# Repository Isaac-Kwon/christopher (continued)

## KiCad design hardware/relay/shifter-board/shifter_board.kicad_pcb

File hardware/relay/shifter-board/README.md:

# 릴레이 시프터 보드 (Phase 3 R 트랙, 회로도)

작성일: 2026-11-15 · 상태: **회로도(KiCad 10) 생성·ERC·넷리스트 시뮬레이션 완료, 기판 배치(부품 배치 + 넷리스트 + 설계 규칙) 완료, 배선은 사용자가 나중에 함. 결정 0003 8.3절(S1–S3) 반영함(10절)** · 관련: `hardware/relay/concept.md` 3·5·7절, `docs/decisions/0001-test-register-timing.md`, `docs/decisions/0003-interfaces.md`(5.2·7.1·8.3절), `hardware/common/design-brief.md`, `hardware/common/unit-tester/README.md`, 기준 모델 `crates/christopher-core/src/relay.rs`

**표기.** **(계산)** = 이 문서의 산술, **(추정)** = 실측 전 값, **(미확인)** = 데이터시트로 확인하지 못한 것.

## 1. 무엇인가

`concept.md` 3.3절의 시프터 보드 **1장** = 이진 5단 시프터 **한 쌍**(가는 길 + 오는 길). 유닛당 4장(a1–a4). 한 단의 같은 선에서 가는 길 접점과 오는 길 접점은 **한 개의 DPDT 릴레이**가 함께 전환한다(두 반쪽이 코일을 공유). 보드 = 5단 × 26 = **릴레이 130개**, 코일 130개, 역기전력 다이오드 130개.

| 파일 | 내용 |
|---|---|
| `gen_shifter.py` | KiCad 프로젝트와 계층 회로도 생성기(표준 라이브러리만 사용). KiCad 표준 심볼 라이브러리에서 심볼을 복사해 넣는다 |
| `shifter_board.kicad_pro`, `shifter_board.kicad_sch` | 생성물. 루트 시트: 커넥터 5개 + 단 시트 5개 + `CHASSIS` 부품(장착 구멍 H1–H4, R6, C1) |
| `stage_1/2/4/8/16.kicad_sch` | 생성물. 단(이동량) 시트: 릴레이 26개 + 다이오드 26개 + 표시 LED |
| `verify_shifter.py` | 넷리스트를 읽어 보드를 시뮬레이션(5절) |
| `gen_shifter_pcb.py`, `shifter_board.kicad_pcb` | 기판 배치 생성기와 생성물(6절). 배선 없음 |
| `verify_shifter_pcb.py` | 배치된 기판 대 회로도 확인 + DRC(6절) |

생성물은 UUID를 고정해 두어 다시 생성해도 차이가 나지 않는다. 손으로 고치지 말고 생성기를 고친다.

## 2. 회로 규약 (`relay.rs`와의 대응)

- 선 번호 i = 0..25 ↔ 글자 A–Z. 네트 이름: `OIN_A`(가는 길 입력) … `OOUT_A`(가는 길 출력), `RIN_A`(오는 길 입력) … `ROUT_A`(오는 길 출력), 단 사이는 `O1_A`..`O4_A`, `R1_A`..`R4_A`.
- 단 b(b = 0..4, 이동량 s = 2^b, 시트 이름 `STAGE_s`, 참조 `K{b+1}{i+1:02}` = K101..K526), 선 i의 릴레이 하나:

| 접점 | 공통(COM) | 상시 닫힘(NC, 코일 off) | 동작 시 닫힘(NO, 코일 on) |
|---|---|---|---|
| 극 1 = 가는 길 반쪽 | 핀 4 ← 입력 `OIN_i` | 핀 3 → 출력 `OOUT_i` | 핀 5 → 출력 `OOUT_(i+s mod 26)` |
| 극 2 = 오는 길 반쪽 | 핀 9 ← 입력 `RIN_i` | 핀 10 → 출력 `ROUT_i` | 핀 8 → 출력 `ROUT_(i−s mod 26)` |

  (G6S-2 핀 기능은 KiCad 심볼 그림에서 확인: 코일 정지 상태에서 극 1의 접극자는 핀 3, 극 2는 핀 10에 닿아 있다. 코일 = 핀 1(+)과 12(−).)
- 한 단의 입력 → 출력, 단 0 → 단 4 순서로 직렬(덧셈은 교환 법칙이 성립하므로 순서 무관). 코일을 켠 단의 이동량 합이 제어값 a(0..25, 합이 25를 넘지 않음).
- **가는 길**: `OIN_i` → `OOUT_(i+a mod 26)`. `relay.rs`의 `shift_binary(c, a, reverse=false)`와 같다.
- **오는 길**: `RIN_i` → `ROUT_(i−a mod 26)`. 오는 길은 같은 제어값으로 가는 길의 시프트를 **되돌린다**(`relay.rs`의 `scramble`에서 가는 길의 `shift_binary(x, a, false)`마다 오는 길에 `shift_binary(x, a, true)`가 대응). 같은 코일이 두 극을 움직이므로 "제어를 따로 두지 않는다"는 concept 2.2절 ②가 그대로 성립한다.
- **모듈을 거꾸로 끼움**(`a4 = l`: 가는 길 −l, 오는 길 +l): 신호가 OUT 커넥터로 들어가 IN 커넥터로 나오면 가는 길 `OOUT_j` → `OIN_(j−a)`, 오는 길 `ROUT_j` → `RIN_(j+a)`. `verify_shifter.py`가 네 방향 모두 확인한다.
- 코일 구동: 단마다 `CTRLb`(24 V) 하나. 단의 코일 26개가 `CTRL`과 0 V 사이에 **병렬**, 코일마다 역기전력 다이오드(1N4148W, 음극 = `CTRL`). 단마다 표시 LED 하나(4.7 kΩ 직렬, 약 4.7 mA, `concept.md` 8절의 "단마다 LED 하나").
- 스크램블러는 유닛의 릴레이 구동기가 `CTRLb`에 24 V를 인가/차단한다(보드에는 능동 소자가 없다). 전환은 무전류 상태에서(`design-brief.md` 4.2절).

## 3. 커넥터와 핀 배치

보드 위 커넥터는 전부 **D-sub 수(핀) 직각 PCB 장착**(`Connector_Dsub:DSUB-37_Pins_Horizontal…`). 근거: `design-brief.md` 12절 결정 11(3.0은 D-sub 37), 시험기 J_A/J_B(암) 와 1:1 케이블로 바로 연결, 선 26개 + 기준선 3개가 37핀에 들어감. 4개를 한 모서리에 놓으면 폭이 맞지 않으므로(D-sub 37 ≈ 66 mm × 4) **IN 두 개(J1, J2)는 한 변, OUT 두 개(J3, J4)는 반대 변**에 놓는 것을 가정한다(변당 약 132 mm, `concept.md`의 160 × 200 mm 안에 듦 **(추정)**).

| 참조 | 이름 | 용도 | 핀 |
|---|---|---|---|
| J1 | OUTBOUND_IN | 가는 길 입력 | 1–26 = 선 A–Z, **27–29 = 0 V 기준선이지만 이 보드에서는 잇지 않음(미접속, `no_connect`)**, 30–37 예약(미접속) |
| J2 | RETURN_IN | 오는 길 입력 | 같음 |
| J3 | OUTBOUND_OUT | 가는 길 출력 | 같음 |
| J4 | RETURN_OUT | 오는 길 출력 | 같음 |
| J5 | CONTROL | 제어·구동(D-sub 9 수) | 1–5 = `CTRL0`..`CTRL4`(가중치 1, 2, 4, 8, 16, 24 V 단 구동), 6–7 = 0 V(**이 보드의 유일한 0 V 복귀**), 8–9 예약(미접속) |

핀 1–26 = 선 A–Z는 시험기 README 3.4절의 J_A/J_B와 같다(전원 핀 없음). 27–29번(0 V 기준선)은 **공통부 쪽(패널·레지스터·시험기)에서만 0 V에 묶고 스크램블러 쪽인 이 보드에서는 잇지 않는다**(결정 0003 5.2절: 양쪽에서 묶으면 코일 복귀 전류가 메뉴 케이블로 나뉘고 케이블을 뽑을 때마다 복귀 경로가 바뀐다). 제어값 a를 이진수로 `CTRL0`..`CTRL4`에 싣는다(비트 b = 이동량 2^b). 시험기는 J_C로 이 제어를 직접 구동하지 않는다. R.1에서는 유닛 쪽 구동기(또는 5개의 스위치 + 24 V)로 구동한다.

## 4. 코일 전류와 전력

릴레이: Omron G6S-2 급 24 V 코일(심볼 `Relay:G6S-2`, 풋프린트 `Relay_THT:Relay_DPDT_Omron_G6S-2`). `concept.md` 4절의 코일 전력 140–200 mW 사용 **(계산)**.

| 항목 | 140 mW | 200 mW |
|---|---:|---:|
| 코일 1개 (24 V) | 5.8 mA | 8.3 mA |
| 한 단 (26개 병렬 + LED 4.7 mA) | 약 157 mA, 3.7 W | 약 222 mA, 5.3 W |
| 최악(제어값 15 또는 23 = 4단 동작) | 약 0.63 A, 15 W | 약 0.89 A, 21 W |
| 평균(0–25 균등, 단 동작률 44%, `concept.md` 7절) | 8.0 W | 11.4 W |
| 유닛(보드 4장) 평균 | 32 W | 46 W |

`concept.md` 7절의 유닛당 32–46 W와 같은 값이다. 코일 한 단의 전류는 J5의 해당 핀 하나를 지난다(D-sub 접점 정격 수 A 이내). 0 V 복귀는 J5 핀 6–7뿐이다(신호 커넥터의 27–29는 잇지 않는다, 0003 S1). 접점 부하는 최대 약 0.2 A·24 V(`concept.md` 7절)로 G6S-2의 2 A·30 V DC 대비 여유가 크다.

## 5. 재생성과 검증

KiCad 10과 Python 3(표준 라이브러리만)이 필요하다. 표준 심볼 라이브러리 위치는 기본 `C:/Program Files/KiCad/10.0/share/kicad`, 다르면 환경 변수 `KICAD_SHARE`. `kicad-cli`는 PATH 또는 `KICAD_CLI`.

```
python gen_shifter.py                      # 회로도 재생성
kicad-cli sch erc --severity-all --format json -o erc.json shifter_board.kicad_sch
python verify_shifter.py                   # 넷리스트 내보내기 + 시뮬레이션 + 음성 시험
kicad-cli sch export pdf -o shifter_board.pdf shifter_board.kicad_sch   # 보고서용 PDF(저장소 밖에 둘 것)
```

- **ERC**(KiCad 10.0.4, 모든 심각도): 위반 **0건**(오류 0, 경고 0). 미사용 핀은 모두 비접속 표시(`no_connect`): J1–J4의 27–37, J5의 8–9.
- **시뮬레이션** `verify_shifter.py`: `kicad-cli`로 계층 넷리스트(kicadsexpr)를 내보내고, 제어값 0..25마다 J5 제어 네트에 코일 핀이 걸린 릴레이를 동작시켜 접점(NC/NO)을 닫은 뒤 합집합-찾기로 연결을 추적한다. 26개 선 × (가는 길, 오는 길, 거꾸로 끼운 가는 길·오는 길)이 `shift_binary`(코드에 옮겨 둔 `relay.rs` 사본)의 (i+a), (i−a), (j−a), (j+a) mod 26과 **정확히 같고 다른 연결은 없음**(우회·단락 없음)을 확인한다. 코일·다이오드 위상(단별 26개, 0 V, 다이오드 방향)과 부품 수(릴레이 130, 다이오드 130)도 확인한다. 0003 항목: J1–J4의 27–29번이 어느 넷에도 묶이지 않음, `CHASSIS`(H1–H4, R6.1, C1.1)가 0 V 넷과 별개이고 R6(1 MΩ) ∥ C1(10 nF)로만 0 V에 닿음, 어떤 제어값에서도 `CHASSIS`가 신호·제어 핀과 이어지지 않음. 결과: 26개 제어값 전부 통과.
- **음성 시험**: 넷리스트 복사본에서 J3 핀 3↔4, J1 핀 1↔2, J4 핀 20↔25, 릴레이 K305의 NC↔NO, J5의 CTRL1↔CTRL2를 바꾸면 모두 검증이 실패한다. 0003 항목으로 J1 핀 27·J4 핀 29를 0 V에 묶기, J5 0 V 핀을 `CHASSIS`에 단락, 장착 구멍 H3을 0 V로 옮기기, R6을 `CHASSIS` 쪽으로 옮기기도 모두 감지된다(10개 모두 감지).
- 회로도 PDF는 저장소 밖의 빌드 디렉터리(Windows: `%LOCALAPPDATA%\christopher\shifter-board`)에 둔다. 용지 A1, 루트 + 단 시트 5장 = 6쪽. `gen_shifter.py`는 `.kicad_pro`를 덮어쓰므로 곧바로 `gen_shifter_pcb.py`를 다시 돌린다.

## 6. 기판 배치 (배선은 사용자가 나중에 함)

범위: **배치만**. 외곽선, 장착 구멍, 모든 풋프린트의 위치·방향, 회로도 넷리스트(래츠넷이 보임), 설계 규칙. 동박 배선·비아·존은 없다(배선 코드는 생성기에 넣지 않았다, 플래그도 없다). `gen_shifter_pcb.py`는 `kicad-cli`로 회로도 넷리스트를 내보내 풋프린트를 KiCad 라이브러리에서 복사해 `shifter_board.kicad_pcb`를 쓰고(표준 라이브러리만 사용, UUID 고정이라 재생성 결과가 바이트 단위로 같다), 같은 이름의 `.kicad_pro`에 보드 설계 규칙을 병합한다. 주의: `gen_shifter.py`를 다시 돌리면 `.kicad_pro`가 덮어쓰이므로 그 뒤에 `gen_shifter_pcb.py`를 다시 돌린다.

**크기: 250 x 228 mm, 4층.** 160 x 200 mm는 들어가지 않는다. G6S-2 풋프린트의 courtyard가 7.9 x 15.3 mm여서 한 열 26개만 해도 26 x 8.0 = 208 mm이고(릴레이 130개의 면적만 약 1.6만 mm2), 선 26개 x 반쪽 2개의 단 사이 이동 배선(이동량 16 단은 위로/아래로 최대 약 21개의 수직 차선이 겹침 **(계산)**)과 커넥터 부채꼴 배선 공간이 더 든다. 그래서 단 사이를 38 mm 간격으로 비워 두었다(배선 채널). 유닛 카드 케이지(`concept.md`)는 이 크기로 바꿔야 한다. 채널 폭은 배선하면서 줄일 수 있다(릴레이 열 사이 간격 38 mm, 행 간격 8.0 mm는 `gen_shifter_pcb.py` 상단 상수).

배치 규칙:
- 릴레이 5열(단 1, 2, 4, 8, 16, 왼쪽에서 오른쪽) x 26행(선 A가 위). 90도 돌려서 신호 흐름이 +x 방향: 핀 순서 1(코일), 3(NC), 4(COM), 5(NO)가 가는 길 행(y), 핀 12, 10, 9, 8이 5.08 mm 위의 오는 길 행. 행 간격 8.0 mm(courtyard 7.9 mm), 열 간격 38 mm.
- 코일 역기전력 다이오드(SOD-123): 각 릴레이의 코일 핀 왼쪽에 세로로(음극이 핀 1 쪽). 왼쪽 6 mm 띠에 단별 CTRL/0 V 수직 레일을 둘 자리가 있다.
- 단 표시용 R + LED: 각 열 아래.
- 커넥터: 왼쪽 변에 J1(가는 길 IN), J2(오는 길 IN), J5(제어, D-sub 9), 오른쪽 변에 J3, J4(OUT). IN은 한 변, OUT은 반대 변. 장착 구멍 M3 4개(모서리, **도금 구멍 `MountingHole_3.2mm_M3_Pad` = 회로도 부품 H1–H4, 넷 `CHASSIS`**), 단 이름 실크. `CHASSIS`–0 V의 R6·C1은 오른쪽 아래.
- `CHASSIS` 넷: D-sub 5개의 껍데기 패드(`SH`, 커넥터마다 2개, 회로도 심볼에는 핀이 없음)와 H1–H4. 생성기가 `SH` 패드에 `CHASSIS`를 붙이고 `verify_shifter_pcb.py`가 같은 규칙으로 회로도 대 기판을 비교한다.
- 같은 규칙으로 정한 층 계획(배선 때 쓰라고 남기는 제안, 강제 아님): 가는 길은 F.Cu(수평)·In1(수직), 오는 길은 B.Cu(수평)·In2(수직), 코일 CTRL 레일 In1, 0 V 레일 In2. 이동 배선은 차선+비아 방식(이동량 s 단의 수직 차선은 가는 길/오는 길 각각 약 3, 5, 9, 17, 21개). 커넥터 팬아웃은 핀 열(1-19, 20-26)별로 단조이므로 층을 나눠 비아 없이 가능하다.

설계 규칙(`.kicad_pro`, 저가 4층 업체 표준): 선폭/간격 0.15 mm, 비아 0.5/0.25 mm(환형 0.125), 구멍 간 0.25 mm, 동박-외곽 0.3 mm. 넷클래스 Default(선폭 0.2)와 Coil(`/CTRL*`, `/GND`, 선폭 0.6 mm: 단 코일 전류 최대 약 0.25 A, 보드 전체 0 V 복귀 최대 약 0.9 A 이므로 0 V 간선은 더 두껍게). 신호 전류는 선 하나 약 10 mA라 0.15-0.2 mm로 충분하다.

확인(`verify_shifter_pcb.py`, 결과 PASS):
- 회로도 부품 281개(275 + H1–H4 + R6 + C1) 전부 기판에 있고 풋프린트가 회로도와 같으며(여분 없음), IPC-D-356 넷리스트의 패드 연결이 회로도 넷과 정확히 같음(1490 패드, `CHASSIS`의 `SH` 패드 10개 포함). 패드 두 개의 넷을 바꾼 복사본, D-sub 껍데기 패드 하나를 `CHASSIS`에서 0 V로 옮긴 복사본은 검출됨(음성 시험 2건). 재생성 결과는 바이트 단위로 같음.
- `kicad-cli pcb drc`(모든 심각도): **위반 0건**(courtyard/겹침/외곽/간격 포함), 연결 안 됨 항목만 존재. 보고서의 연결 안 됨 목록은 약 500건에서 잘리므로(499건 표시) 래츠넷 수는 pcbnew 연결성으로 센다: **1125** = Σ(핀 수 − 1) (회로도 넷 기준 1115 + 껍데기 패드 10).
- 렌더(`kicad-cli pcb render`)와 PDF를 빌드 디렉터리에 둠. 가버/드릴은 배선 후에(저장소 밖 `%LOCALAPPDATA%\christopher\shifter-board`).

```
python gen_shifter_pcb.py
python verify_shifter_pcb.py
kicad-cli pcb render --side top --width 2400 --height 2200 -o <빌드 디렉터리>/render_top.png shifter_board.kicad_pcb
```

### 6.1 S4 변형 (`--variant s4`, 앞을 보는 a4용)

`python gen_shifter_pcb.py --variant s4` → **`shifter_board_s4.kicad_pcb`**(+ `.kicad_pro`). 회로도·넷리스트는 `shifter_board.kicad_sch` 그대로(패드 넷이 표준 기판과 완전히 같음), 외곽 250 x 228, 구멍 4개, 릴레이·다이오드·표시등·R6·C1·J5도 표준과 같은 자리다. 바뀌는 것은 **J1–J4뿐**이다:

| 커넥터 | 표준 (앞면 F.Cu) | S4 변형 (**뒷면 B.Cu**, 거울) |
|---|---|---|
| J1 | 왼쪽 변, 핀 1 위(y 22.28), 회전 270 | 왼쪽 변, 핀 1 아래(y 72.13), 회전 90 |
| J2 | 왼쪽 변, y 96.29, 회전 270 | 왼쪽 변, y 146.14, 회전 90 |
| J3 | 오른쪽 변, y 72.13, 회전 90 | 오른쪽 변, y 22.28, 회전 270 |
| J4 | 오른쪽 변, y 146.14, 회전 90 | 오른쪽 변, y 96.29, 회전 270 |

핀 행(49.86 mm)의 중심과 변, 몸체가 보드 밖을 향하는 방향은 같고(핀 위치를 pcbnew로 읽어 확인: 변형의 J1 핀 1·19·20이 표준 J3의 같은 핀 좌표와 같음) **핀 1의 끝만 반대**다. 신호 배정(J1 가는 길 IN, J2 오는 길 IN, J3 가는 길 OUT, J4 오는 길 OUT)은 그대로다.

왜 뒷면 거울인가: 앞을 보는 카드는 뒤를 보는 카드와 반대쪽에서 보이므로, 표준 기판을 앞으로 꽂으면 S4.J1–U.J3, S4.J2–W_L.J4, S4.J3–W_L.J1, S4.J4–U.J2의 양 끝 소켓에서 핀 1이 반대 끝에 온다(D-sub는 키가 있어 리본을 뒤집을 수 없다). 평면 회전(180도 또는 좌우 바꿈)은 쌓기에서의 변·자리를 바꾸거나 같은 결과를 내므로, 핀 1의 끝을 돌리는 것은 부품면을 바꾼 거울뿐이다. 부수 효과: S4의 소켓이 뒤를 향해 S4 점퍼가 25 / 50 mm가 된다(표준이면 앞면 쪽 +14로 39 / 64). 실크에 큰 글씨로 `S4 / a4 - FRONT`와 거울 표시가 있다. `verify_shifter_pcb.py`는 두 기판 모두 DRC 0건, 패드 넷 = 회로도, 래츠넷 1125, 재생성 바이트 동일을 확인하고, 변형이 표준과 J1–J4(뒷면, 핀 1 반대 끝, 핀 행 중심 유지) 외에 같음과 실크 표시를 확인한다. 쌓기에서 핀 1 정렬은 `wiring-cards/verify_cards.py`.

### 6.2 표준 기판에 커넥터만 뒷면으로 납땜하면? (검토 후 **기각**)

생각: S4도 표준 기판을 쓰고 J1–J4(직각 D-sub)를 뒤집어 뒷면에서 같은 구멍에 꽂는다(별도 기판 없음). 커넥터 몸체가 보드 밖을 향해야 하므로 몸체 축(핀 행에 수직)을 중심으로 돌려 꽂는 것만 가능하고, 핀 행 방향 좌표가 거울이 되며 두 핀 행은 그대로다. 풋프린트의 실제 패드 좌표(행 1 = 핀 1–19, y 0, 간격 2.77; 행 2 = 핀 20–37, y 2.84, 반 칸 어긋남)로 구한 **σ**(뒷면 커넥터의 핀 k가 들어가는 표준 구멍의 핀 번호):

| 행 | σ(k) |
|---|---|
| 1 (k = 1..19) | 20 − k (1↔19, 2↔18, …) |
| 2 (k = 20..37) | 57 − k (20↔37, 21↔36, …) |

표준 기판의 동박·넷은 구멍에 고정이므로 뒷면 커넥터의 핀 k는 표준 핀 σ(k)의 넷을 싣는다. 점퍼는 곧은 1:1 리본이라 이웃 카드(표준 커넥터)의 핀 k = 선 k가 S4의 핀 k에 닿는다. 결과: **선 A–S(핀 1–19)는 거꾸로(A↔S, B↔R, …) 연결되고 선 T–Z(핀 20–26)는 S4의 31–37번(비접속) 구멍으로 가서 끊긴다**(S4의 선 T–Z는 핀 31–37에 나와 이웃 카드의 31–37번은 연결이 없다). 커넥터의 역할(J1 = 가는 길 입력 …)은 구멍이 같으므로 바뀌지 않는다. 핀 1의 끝은 뒤집히므로 앞을 보는 카드라면 14가닥의 핀 1 정렬은 맞는다(S4 변형과 같은 끝). 그러나 전기적으로는 틀린다.

`wiring-cards/verify_cards.py`(`back_assembled_study`)가 풋프린트 패드 좌표에서 σ를 구해 같은 합성 유닛에 넣었다(리본 끝의 핀 k를 구멍 σ(k)에 연결):

| S4 방향 | 핀 1 정렬(점퍼 14가닥) | 합성 유닛 대 스크램블러 |
|---|---|---|
| 앞 | 14/14 정렬 | 60 Enigma I 순서 × 10 위치 = 600건 0건 일치(선의 약 9%만 맞음), 한 순서 전수 17,576 위치 0건 일치 |
| 뒤 | 4가닥(S4.J1–J4) 어긋남 | 같은 600건 0건 일치, 전수 0건 일치(a4가 거꾸로가 아닌 이중 오류) |

σ는 한쪽 끝만 바뀌는 순열이 아니라 **일부 선이 끊기는** 사상이어서 쌓기에서 흡수할 수 없다(이웃 카드 W·U도 같은 방식으로 뒤집으면 핀 1이 다시 어긋나고, 14가닥 전부가 W·S3 등 다른 카드와 이어져 있다). 흡수하려면 핀 k ↔ σ(k)로 엇갈린 맞춤 케이블 4가닥이 필요한데, 압접 리본은 1:1 곧은 선이라는 설계(3.4절)에 반한다. 따라서 **S4는 6.1절의 변형 기판**(핀 번호가 커넥터를 따라 돌아가므로 패드 n = 선 n)을 쓴다. 변형 기판은 커넥터가 뒷면에 있고 *패드 번호가 풋프린트의 거울을 따라가며 넷이 그 패드에 붙는다*는 점이 이 안과 다르다.

### 6.3 그 밖에 검토한 안 (2026-11-15, 사용자 결정: **변형 기판 유지**)

| 안 | 내용 | 판단 |
|---|---|---|
| 둥근 D-sub 케이블 | 표준 기판 그대로, S4 둘레 4곳만 암-암 1:1 둥근 케이블(자유롭게 꼬이므로 핀 1 문제 없음) | 전기적으로는 맞다. 그러나 지름 약 10 mm, 후드 약 15 mm, 굽힘 반경 수 cm라 25 mm 카드 간격 안에 못 들어가 적층 밖으로 고리를 내야 함(유닛당 4개, 12유닛 48개). 기각. R.1에서 변형 기판 주문 전 임시 시험용으로만 쓸 수 있음 |
| 한 기판에 D-sub 8개(듀얼 풋프린트) | 표준 J1–J4와 변형 J1–J4를 한 기판에 두고 한 세트만 실장 | 같은 자리: D-sub 구멍 배열이 대칭이라 두 세트의 구멍이 겹치는데 구멍마다 넷이 달라 불가. 변을 따라 다른 자리: 왼쪽 변에 남는 길이 약 36 mm(D-sub 37은 70.4 mm), 이웃 카드 커넥터와 마주 보지 않아 곧은 리본이 안 됨. 안쪽으로 약 5 mm 물린 뒷면 겹침(패드 Ø1.6, 열 간격 2.84 mm라 이만큼 필요)만 가능하지만 짝 면이 기판 끝보다 안쪽이 되어 IDC 플러그 간섭·이웃 카드와 5 mm 어긋남, 신호 104가닥이 패드 두 곳씩이라 배선 밀도 두 배. 얻는 것은 기판 종류 하나 감소뿐. 기각 |

## 7. 열린 질문

1. **코일 극성.** G6S-2(단안정, 극성 있음 **(미확인)**)의 코일 + 단자가 핀 1인지 데이터시트로 확인. 회로도는 핀 1 = +, 핀 12 = −로 가정(다이오드 방향 포함).
2. **부품 확정.** 24 V 코일 품번(`G6S-2` 24 VDC 계열), 풋프린트 `Relay_THT:Relay_DPDT_Omron_G6S-2`(관통 구멍)의 장착 면적 대 SMD 변형(`G6S-2F/-2G`), 호환품 사용 여부(`concept.md` 12절 위험 7).
3. **보드 크기와 커넥터 배치.** 160 × 200 mm에는 들어가지 않음(6절): 250 × 228 mm로 배치함, 유닛 카드 케이지 치수 갱신 필요. 배선 후 채널을 좁혀 줄일 수 있음. IDC 2 × 20 대안은 미검토.
4. **배선: 사용자가 나중에 함(6절의 층 계획 참고).** **배선 혼잡.** 단 16(±16칸)과 단 8의 교차 배선이 가장 길다. 선 순서대로 릴레이를 한 줄에 놓고 층수(4층?)·선 폭을 정한다. 직렬 접점 5개(반쪽당)의 접촉 저항 누적과 24 V 신호 간격.
5. **역기전력 다이오드와 복귀 시간.** 다이오드만 쓰면 복귀가 느리다(`decision 0001`의 3–5 ms **(추정)**). 시험 후 필요하면 다이오드 + 제너 또는 저항 병렬.
6. **보호.** (닫힘, 0003 S3) 이 보드에는 퓨즈·역극성 보호·TVS를 두지 않는다. 전원 입력이 없고 `CTRL` 선은 계수기 유닛 보드의 퓨즈(4 A) 뒤다(0003 6절, 7.3절). 접지는 `CHASSIS`(10절 참고).
7. **거꾸로 끼우기의 실현.** 커넥터가 IN/OUT 반대 변이라 보드를 뒤집어 끼우는 방식은 아니다. a4(가는 길 −l)는 케이블/백플레인에서 IN과 OUT을 맞바꿔 연결하는 것으로 구현한다(시뮬레이션은 이 방향도 검증함). 백플레인 설계에서 확정.
8. **시험점·표시.** 선별 시험점, 단 LED 위치, 참조 번호 실크(K101..K526 읽기 쉬운 배치), 단 LED 저항값(4.7 kΩ) 확정.
9. **시험기 연동.** (닫힘, 0003 S1) 27–29번은 공통부(시험기 포함) 쪽에서만 0 V에 묶고 이 보드에서는 잇지 않는다. 시험기의 J_A/J_B 27–29 = GND_F는 그대로다.

## 10. 결정 0003 반영 (8.3절)

| # | 변경 | 상태 |
|---|---|---|
| S1 | J1–J4의 27–29번을 0 V에서 뗌(`no_connect`). 0 V의 복귀는 J5의 6–7번만 | 적용. `verify_shifter.py`가 27–29번의 무연결을 검사하고 음성 시험 2건(J1.27, J4.29를 0 V에 묶기) |
| S2 | 껍데기(J1–J5)와 장착 구멍(H1–H4)을 `CHASSIS`로, `CHASSIS`–0 V에 R6 1 MΩ ∥ C1 10 nF/100 V | 적용. 루트 시트에 H1–H4(`Mechanical:MountingHole_Pad`, 도금 M3), R6, C1. 껍데기 패드 `SH`는 심볼에 핀이 없어 기판 생성기가 `CHASSIS`를 직접 붙이고 검증기가 같은 규칙으로 확인. 음성 시험 3건(0 V 핀을 `CHASSIS`에 단락, H3을 0 V로, R6을 `CHASSIS` 쪽으로) + 기판 음성 시험 1건(껍데기 패드를 0 V로) |
| S3 | 7절 6번(보호)·9번(27–29번)을 닫음. 보드에 퓨즈를 두지 않음 | 적용(7절의 6번·9번) |
| S4 | 바뀌지 않는 것: 암수(핀), J1–J4의 1–26번, J5의 핀 배치, 릴레이·다이오드 | 확인(시뮬레이션 26값 × 4방향 통과) |

장착 구멍은 도금 구멍이 되었다(풋프린트 `MountingHole_3.2mm_M3_Pad`). 금속 기둥으로 프레임(PE)에 닿게 하는 것은 기구 설계의 몫이다.

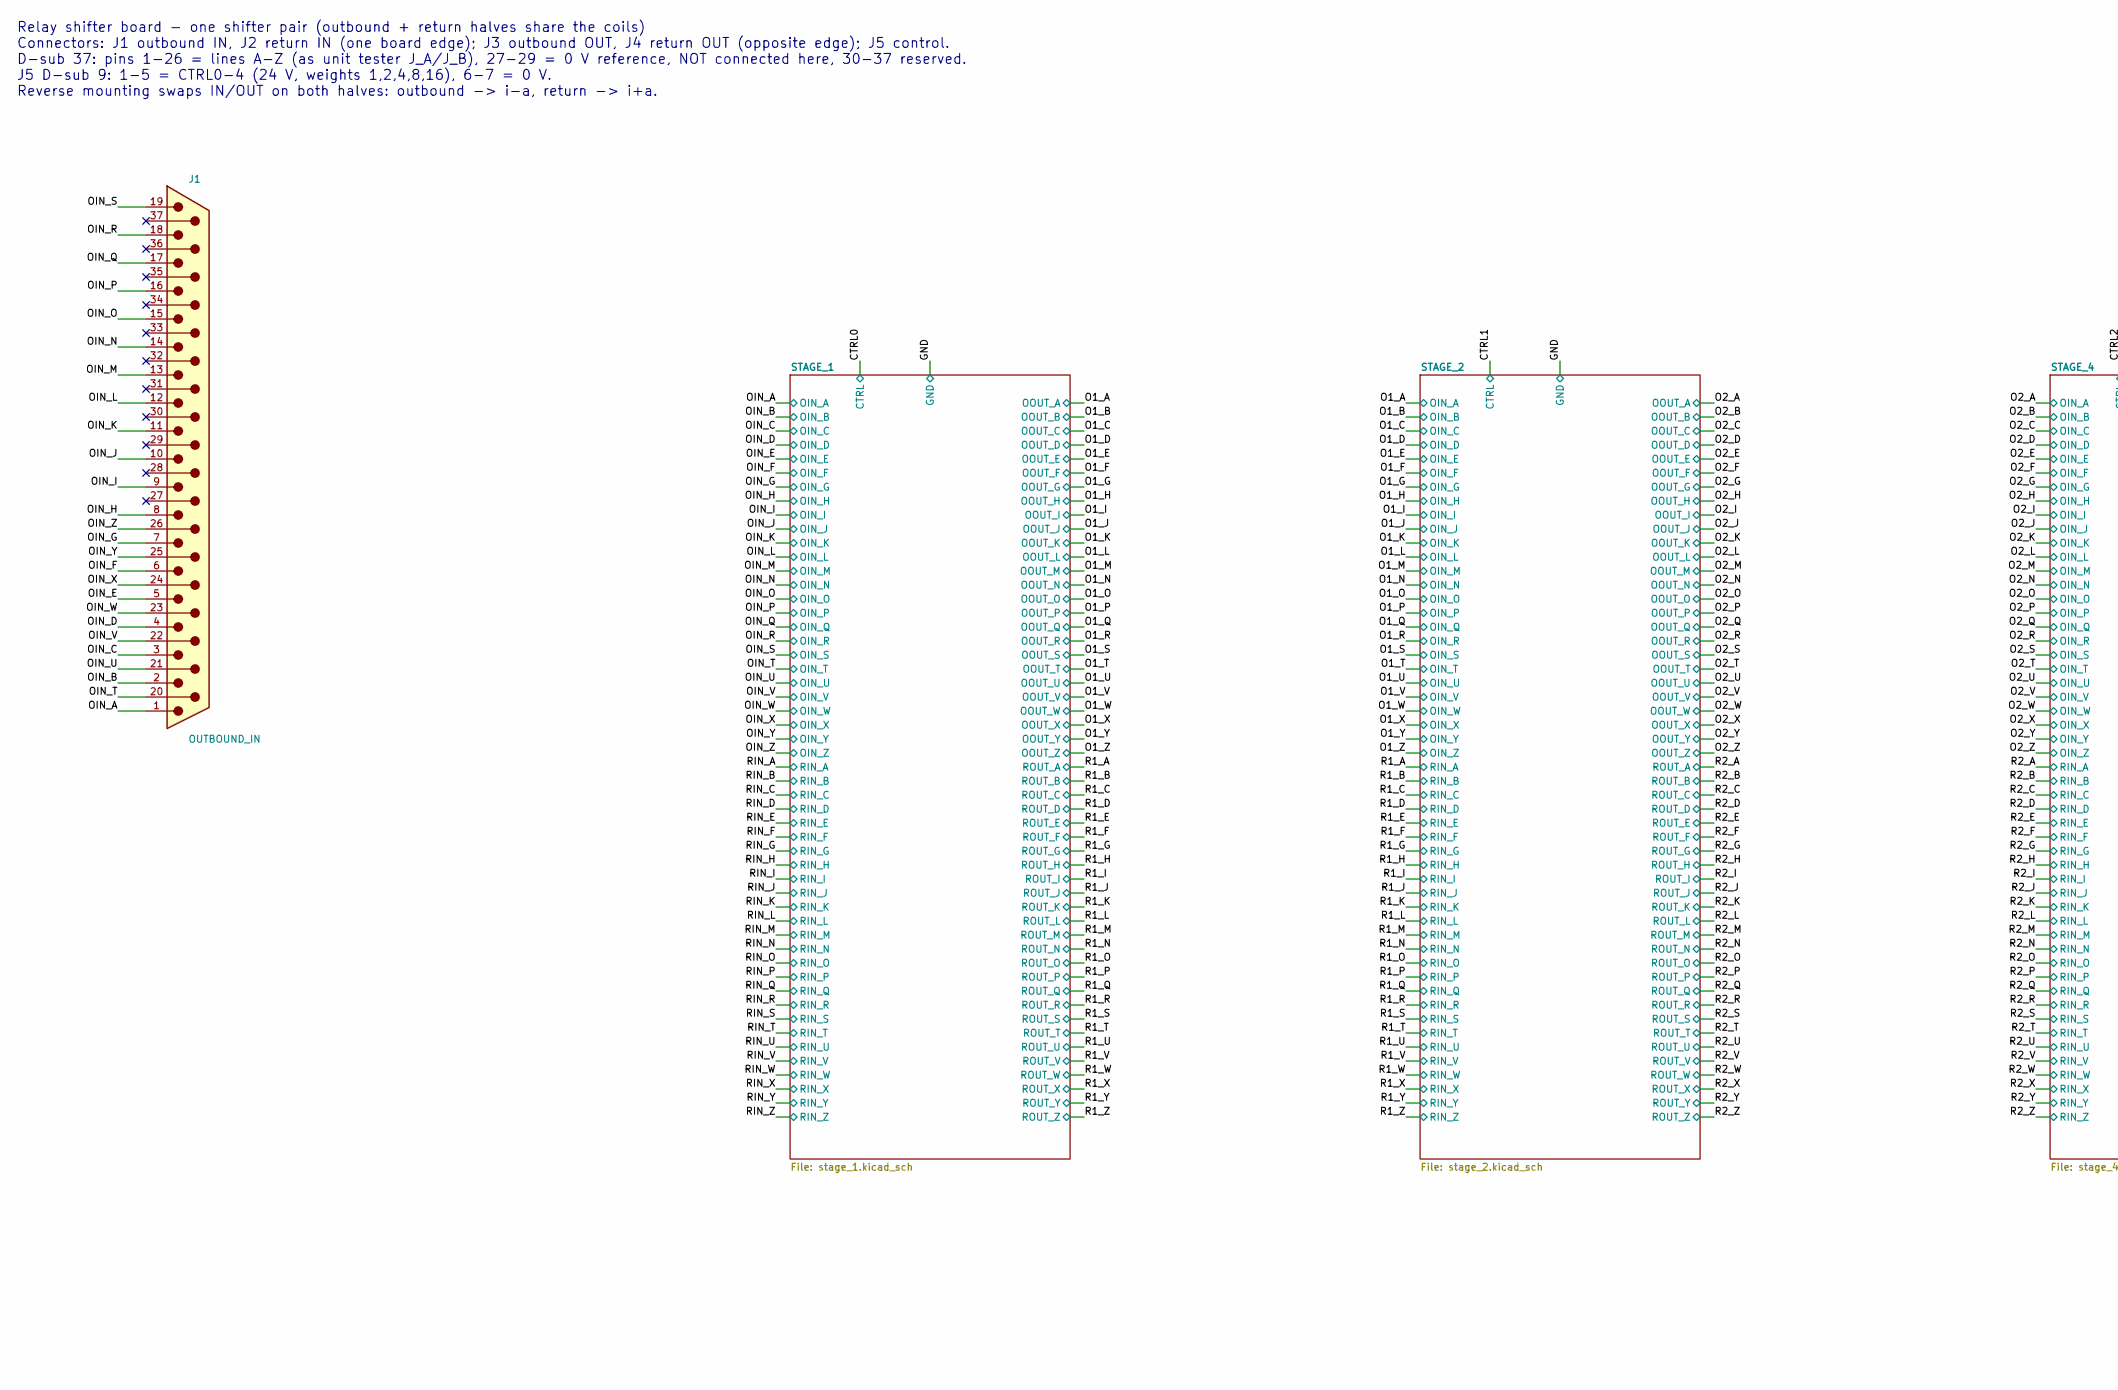
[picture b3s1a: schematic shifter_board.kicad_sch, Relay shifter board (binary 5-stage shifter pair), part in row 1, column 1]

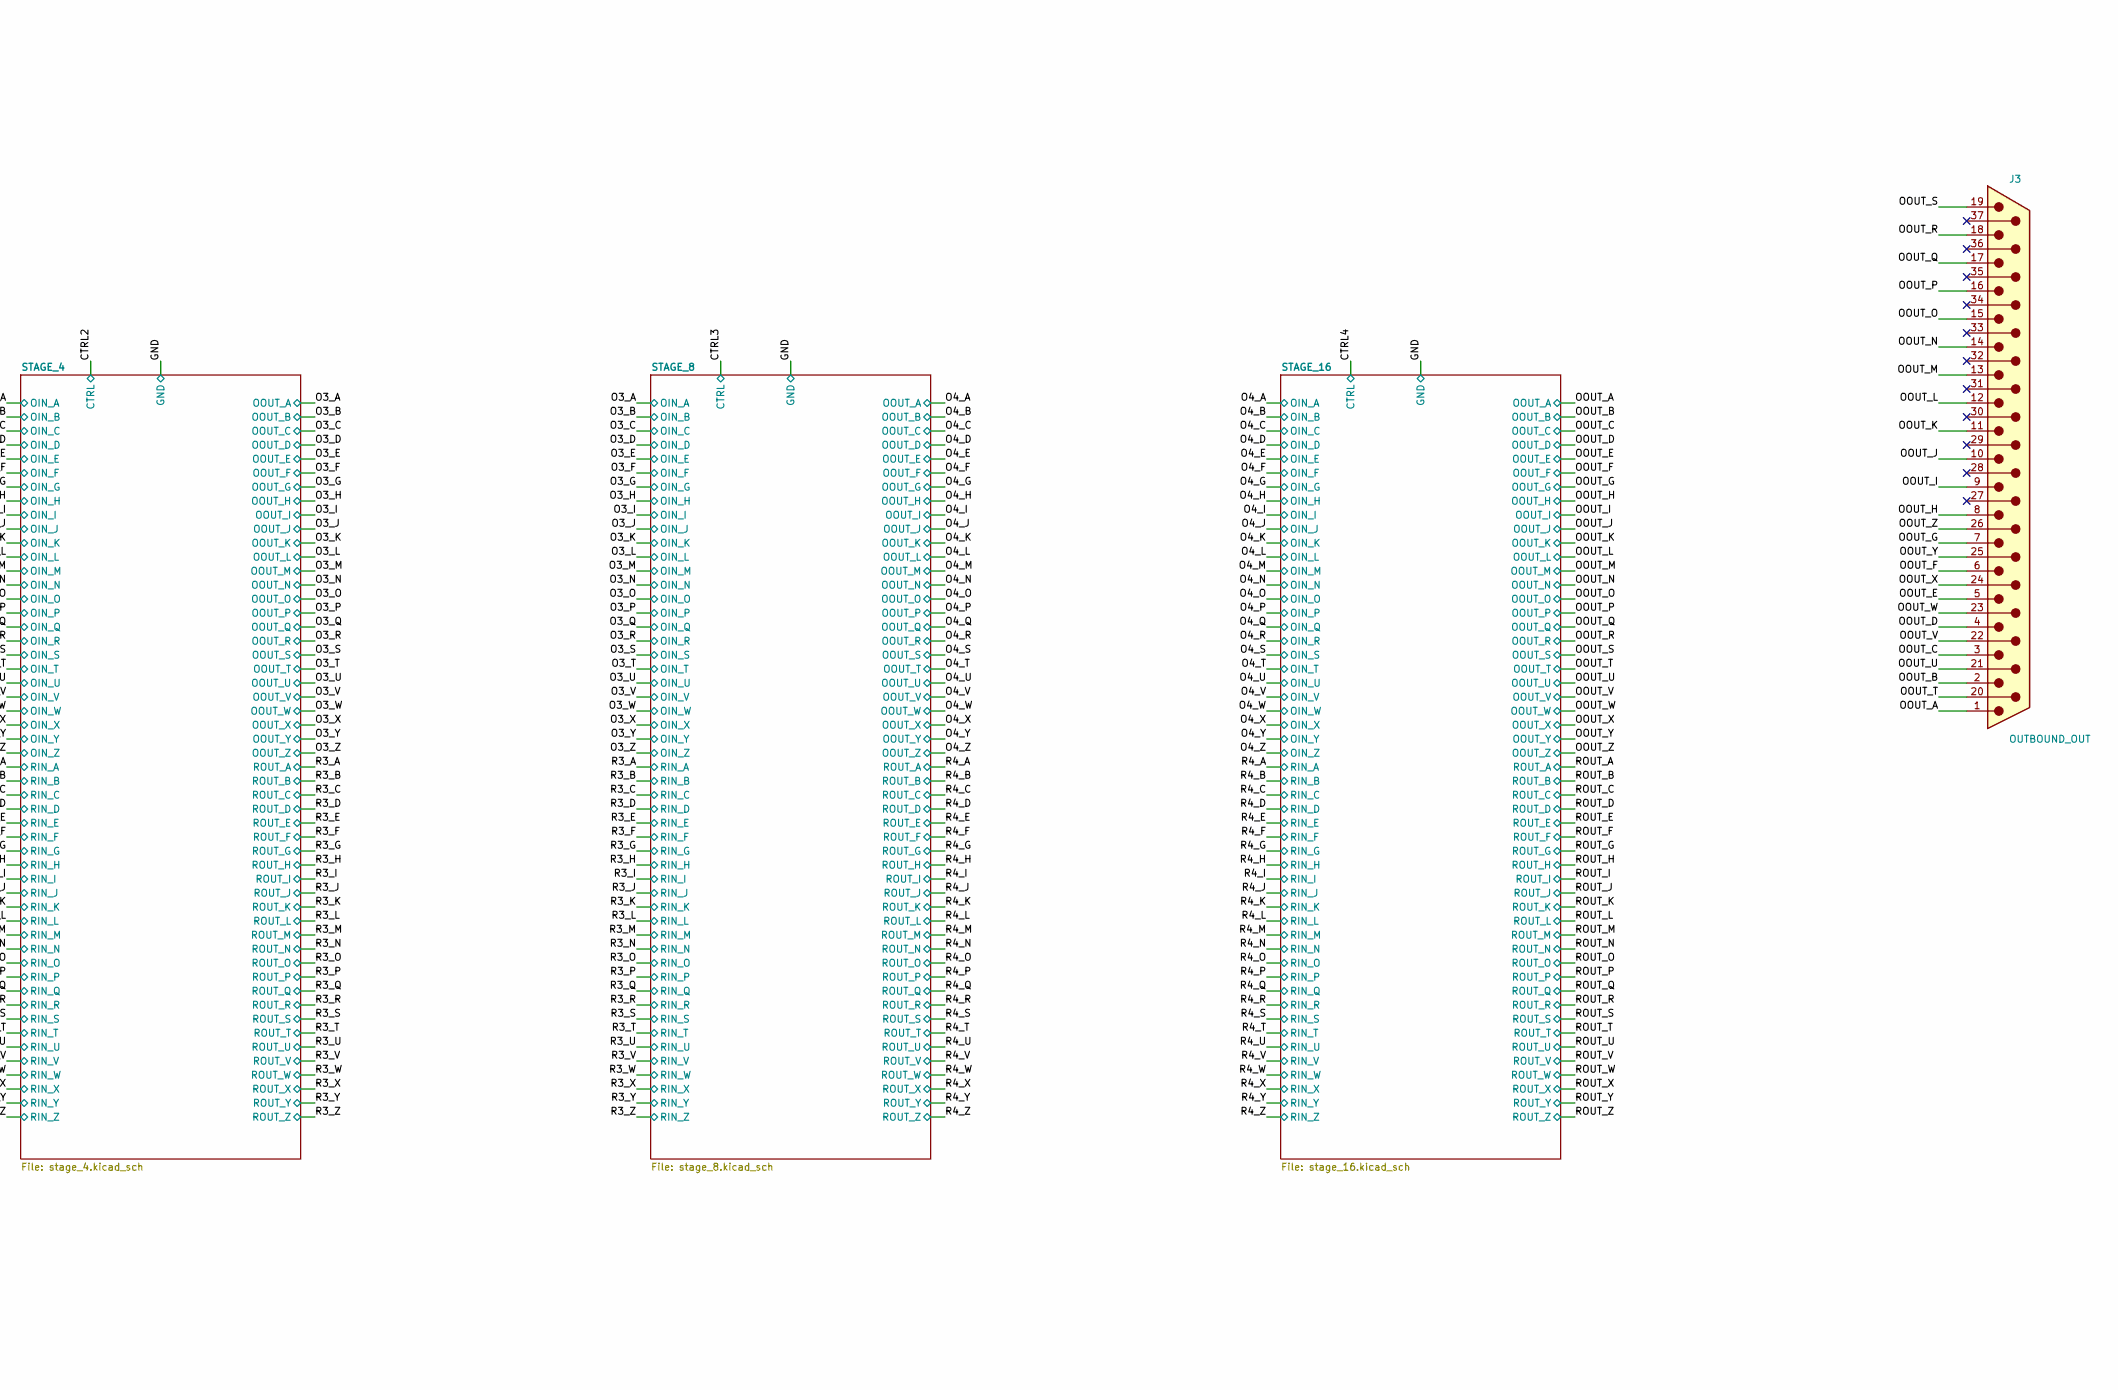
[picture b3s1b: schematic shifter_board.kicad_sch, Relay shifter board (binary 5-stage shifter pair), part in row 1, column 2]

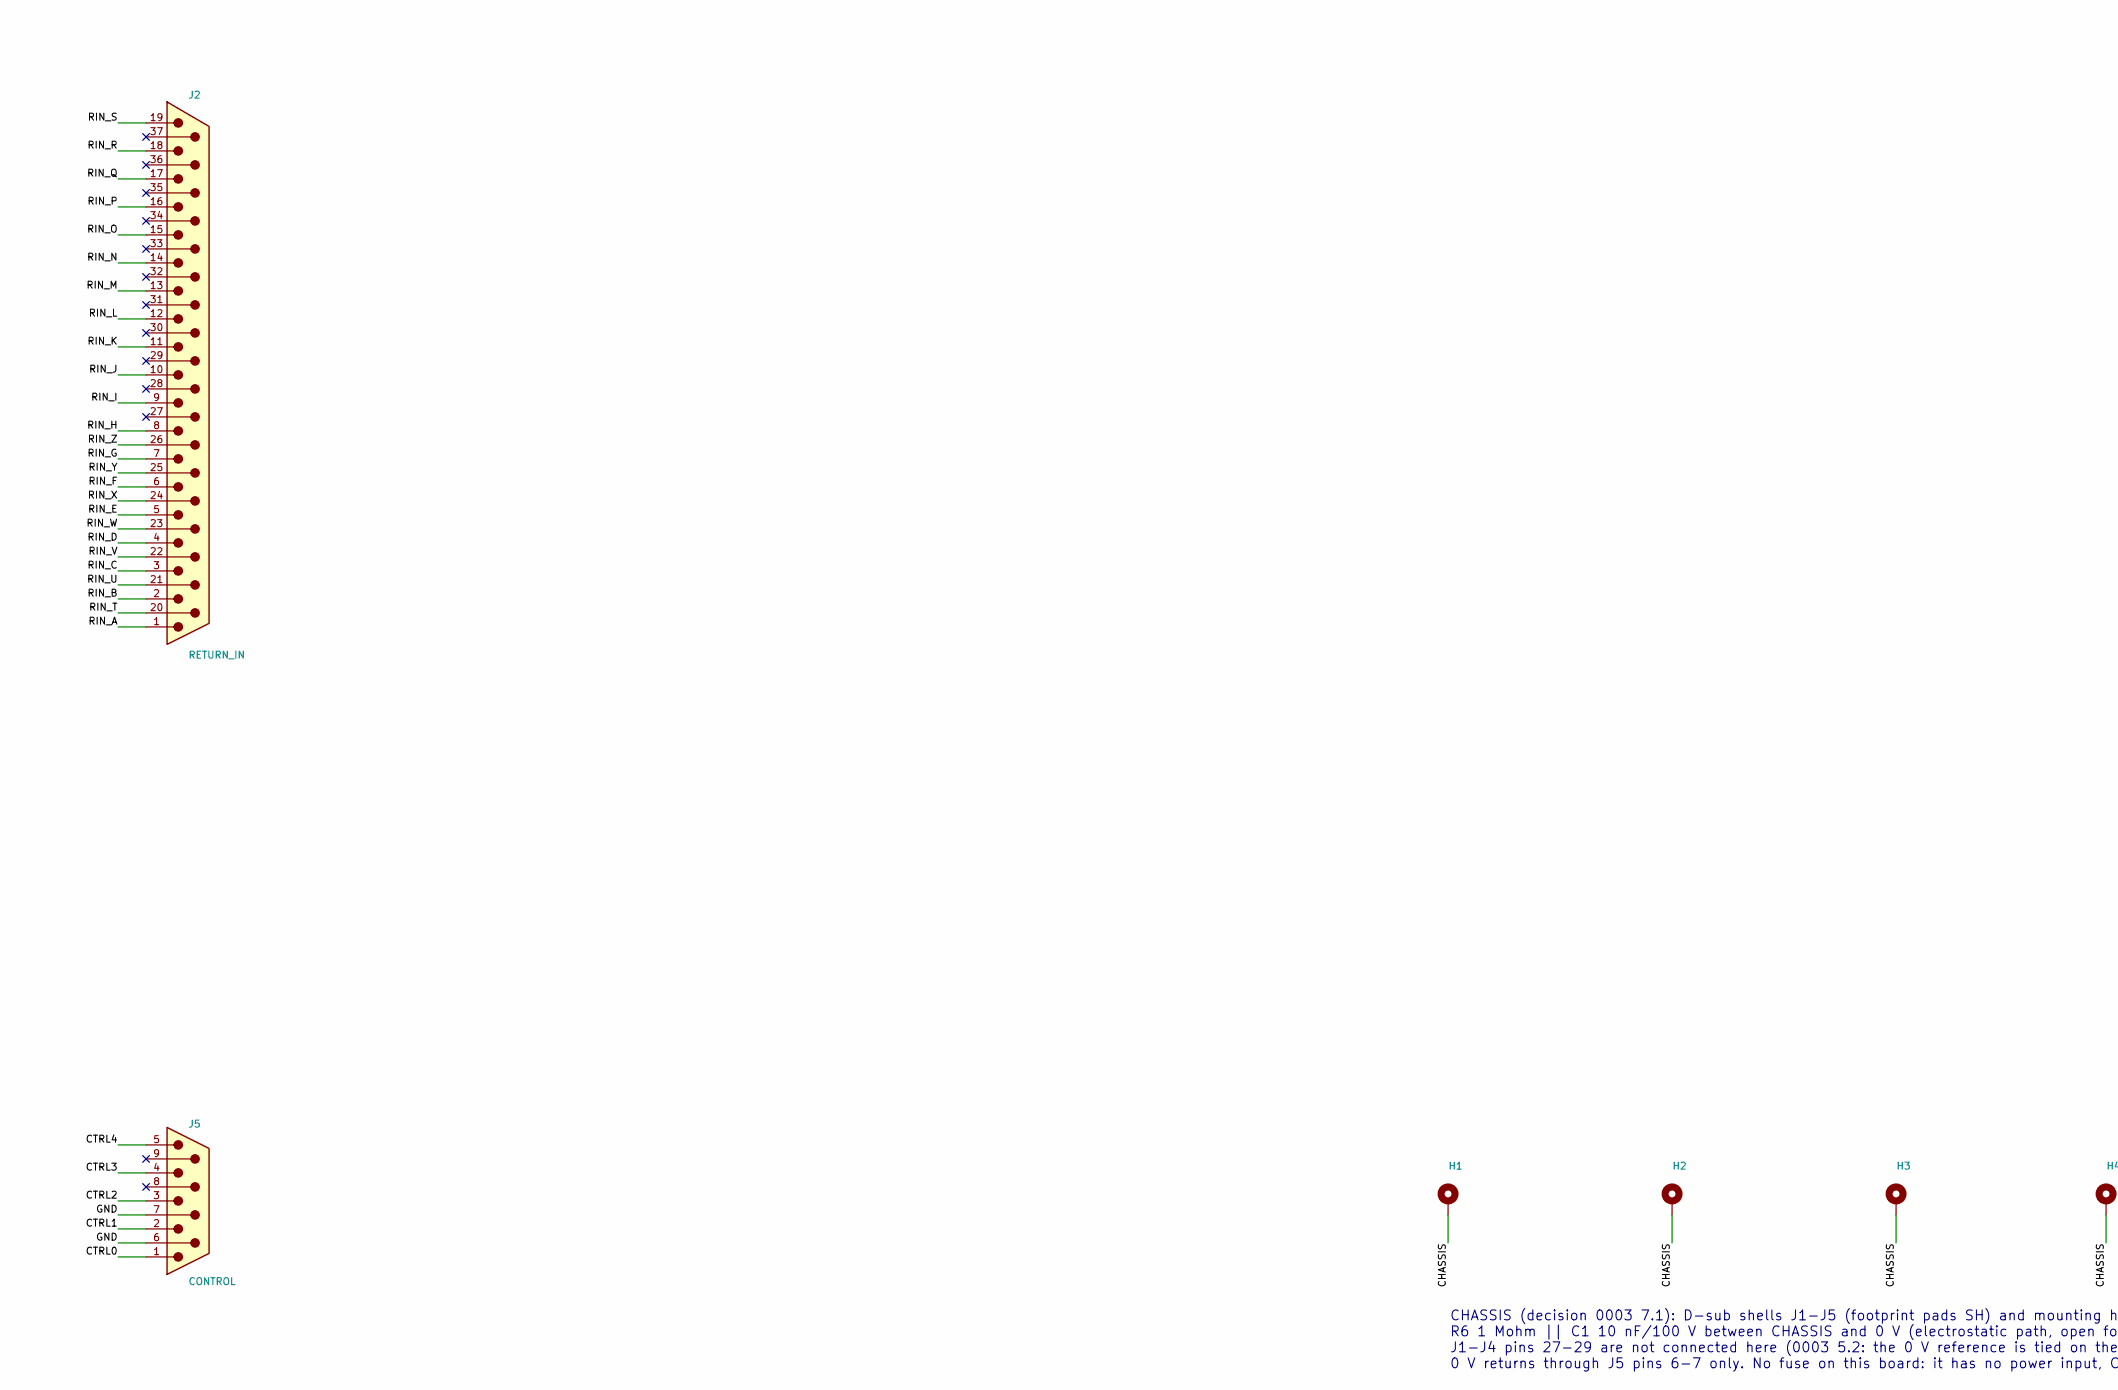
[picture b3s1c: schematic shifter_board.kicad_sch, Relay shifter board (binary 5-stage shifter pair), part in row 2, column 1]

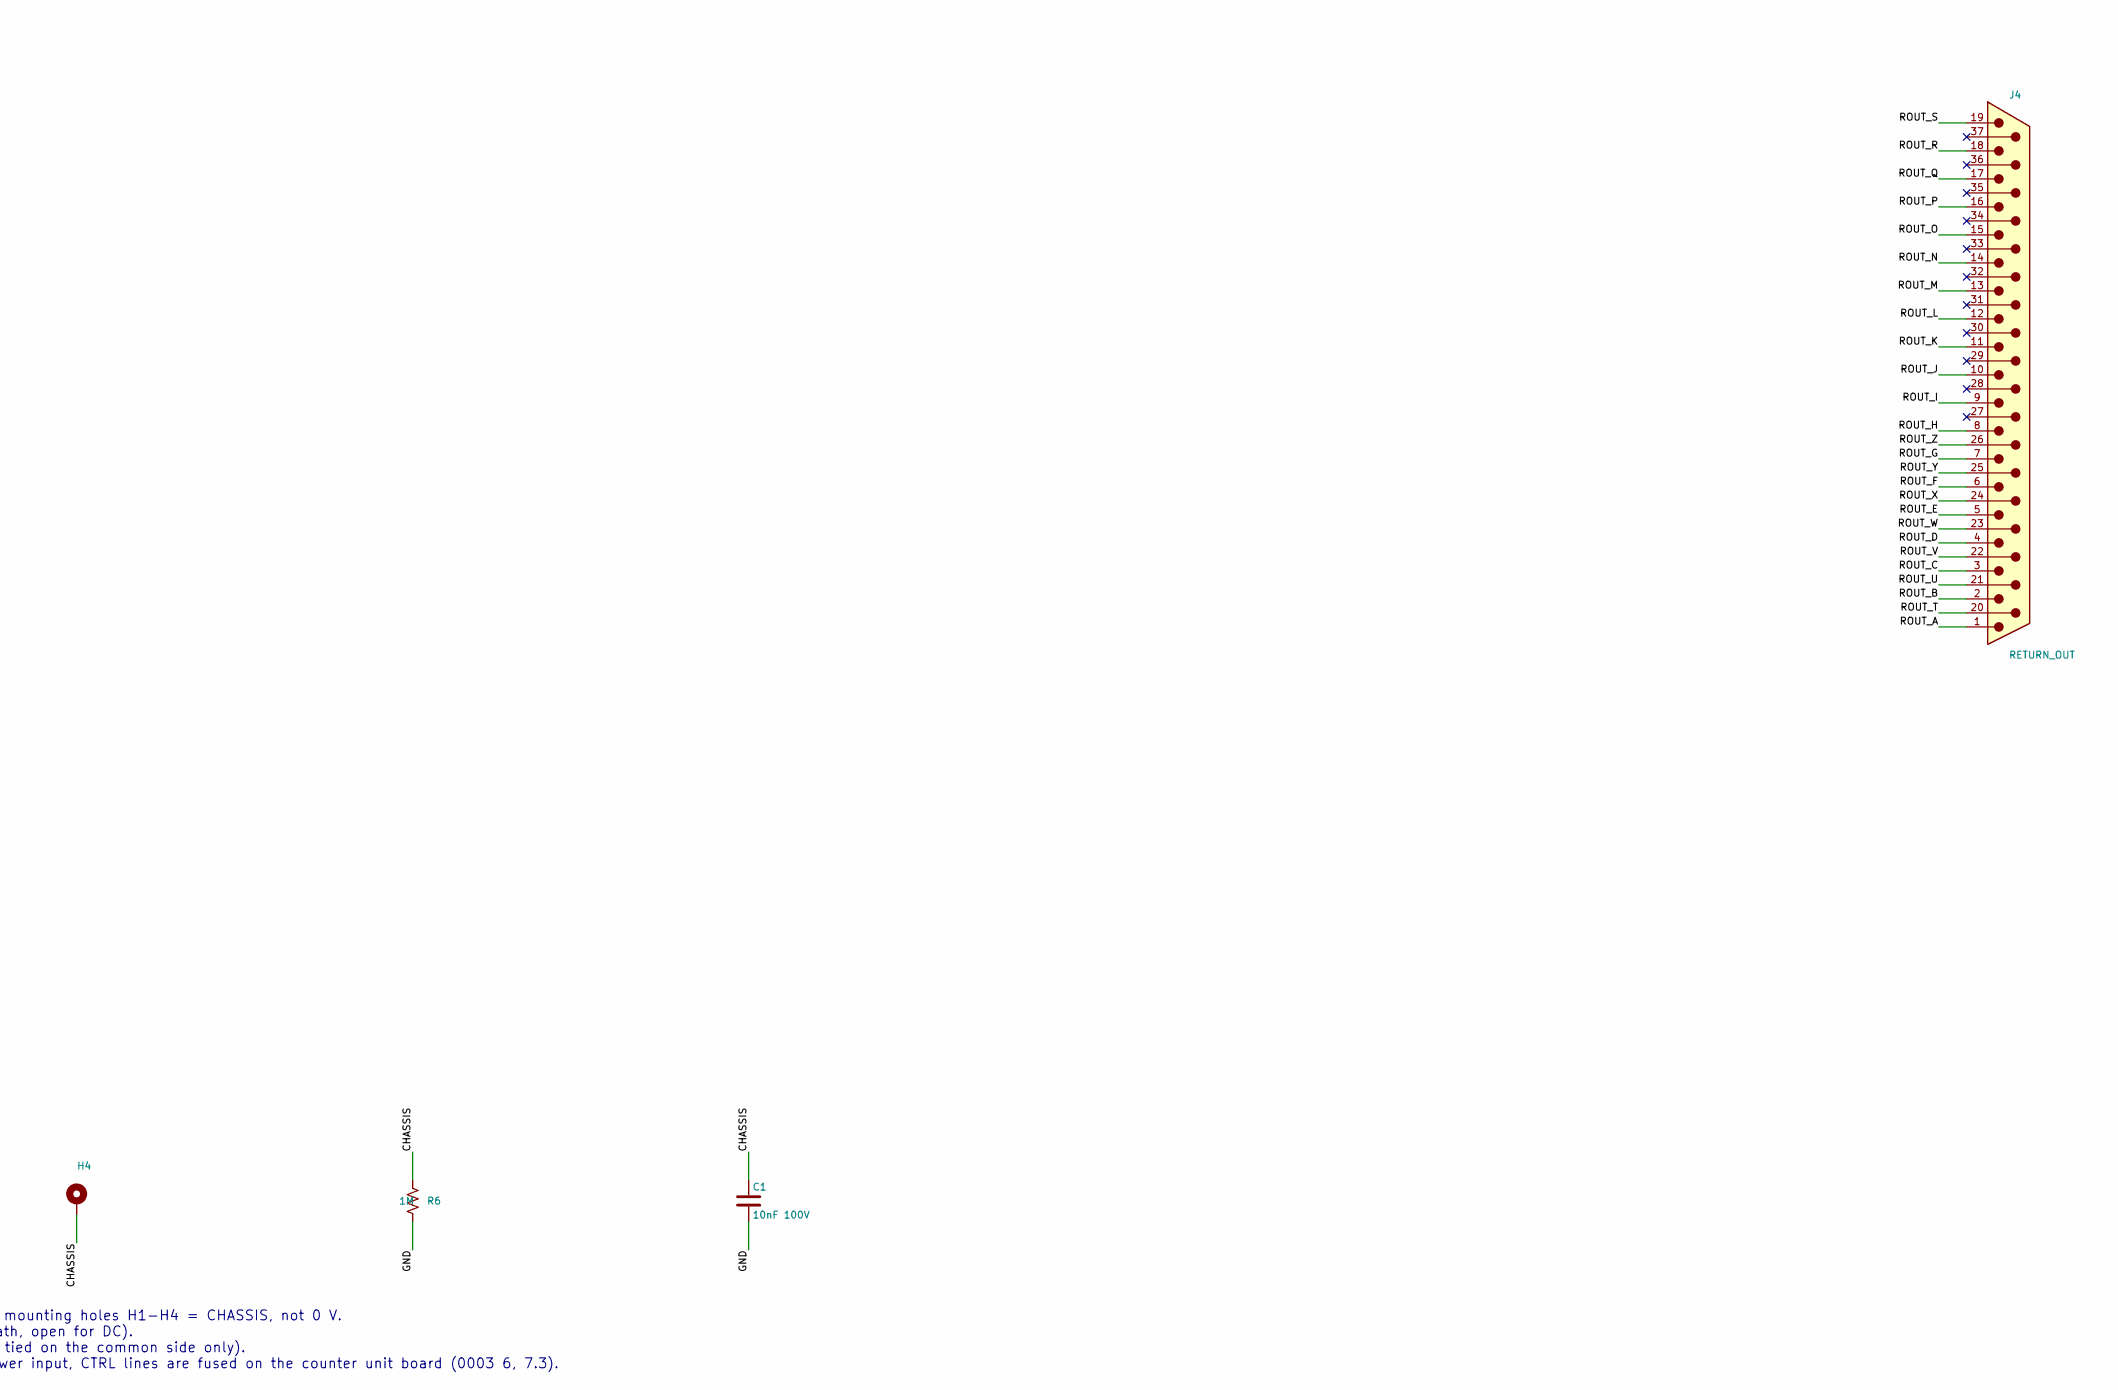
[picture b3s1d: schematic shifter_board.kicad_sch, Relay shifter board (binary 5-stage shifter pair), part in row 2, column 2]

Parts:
C1: 10nF 100V; C_0603_1608Metric
H1, H2, H3, H4: MountingHole_Pad; MountingHole_3.2mm_M3_Pad
J1: OUTBOUND_IN; DSUB-37_Pins_Horizontal_P2.77x2.84mm_EdgePinOffset9.90mm_Ho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
J2: RETURN_IN; DSUB-37_Pins_Horizontal_P2.77x2.84mm_EdgePinOffset9.90mm_Ho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
J3: OUTBOUND_OUT; DSUB-37_Pins_Horizontal_P2.77x2.84mm_EdgePinOffset9.90mm_Ho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
J4: RETURN_OUT; DSUB-37_Pins_Horizontal_P2.77x2.84mm_EdgePinOffset9.90mm_Ho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
J5: CONTROL; DSUB-9_Pins_Horizontal_P2.77x2.84mm_EdgePinOffset9.90mm_Hou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
R6: 1M; R_0603_1608Metric

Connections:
/CHASSIS: C1.1, H1.1, H2.1, H3.1, H4.1, J1.SH, J2.SH, J3.SH, J4.SH, J5.SH, R6.1
/CTRL0: J5.1; also elsewhere on the board
/CTRL1: J5.2; also elsewhere on the board
/CTRL2: J5.3; also elsewhere on the board
/CTRL3: J5.4; also elsewhere on the board
/CTRL4: J5.5; also elsewhere on the board
/GND: C1.2, J5.6, J5.7, R6.2; also elsewhere on the board
/OIN_A: J1.1; also elsewhere on the board
/OIN_B: J1.2; also elsewhere on the board
/OIN_C: J1.3; also elsewhere on the board
/OIN_D: J1.4; also elsewhere on the board
/OIN_E: J1.5; also elsewhere on the board
/OIN_F: J1.6; also elsewhere on the board
/OIN_G: J1.7; also elsewhere on the board
/OIN_H: J1.8; also elsewhere on the board
/OIN_I: J1.9; also elsewhere on the board
/OIN_J: J1.10; also elsewhere on the board
/OIN_K: J1.11; also elsewhere on the board
/OIN_L: J1.12; also elsewhere on the board
/OIN_M: J1.13; also elsewhere on the board
/OIN_N: J1.14; also elsewhere on the board
/OIN_O: J1.15; also elsewhere on the board
/OIN_P: J1.16; also elsewhere on the board
/OIN_Q: J1.17; also elsewhere on the board
/OIN_R: J1.18; also elsewhere on the board
/OIN_S: J1.19; also elsewhere on the board
/OIN_T: J1.20; also elsewhere on the board
/OIN_U: J1.21; also elsewhere on the board
/OIN_V: J1.22; also elsewhere on the board
/OIN_W: J1.23; also elsewhere on the board
/OIN_X: J1.24; also elsewhere on the board
/OIN_Y: J1.25; also elsewhere on the board
/OIN_Z: J1.26; also elsewhere on the board
/OOUT_A: J3.1; also elsewhere on the board
/OOUT_B: J3.2; also elsewhere on the board
/OOUT_C: J3.3; also elsewhere on the board
/OOUT_D: J3.4; also elsewhere on the board
/OOUT_E: J3.5; also elsewhere on the board
/OOUT_F: J3.6; also elsewhere on the board
/OOUT_G: J3.7; also elsewhere on the board
/OOUT_H: J3.8; also elsewhere on the board
/OOUT_I: J3.9; also elsewhere on the board
/OOUT_J: J3.10; also elsewhere on the board
/OOUT_K: J3.11; also elsewhere on the board
/OOUT_L: J3.12; also elsewhere on the board
/OOUT_M: J3.13; also elsewhere on the board
/OOUT_N: J3.14; also elsewhere on the board
/OOUT_O: J3.15; also elsewhere on the board
/OOUT_P: J3.16; also elsewhere on the board
/OOUT_Q: J3.17; also elsewhere on the board
/OOUT_R: J3.18; also elsewhere on the board
/OOUT_S: J3.19; also elsewhere on the board
/OOUT_T: J3.20; also elsewhere on the board
/OOUT_U: J3.21; also elsewhere on the board
/OOUT_V: J3.22; also elsewhere on the board
/OOUT_W: J3.23; also elsewhere on the board
/OOUT_X: J3.24; also elsewhere on the board
/OOUT_Y: J3.25; also elsewhere on the board
/OOUT_Z: J3.26; also elsewhere on the board
/RIN_A: J2.1; also elsewhere on the board
/RIN_B: J2.2; also elsewhere on the board
/RIN_C: J2.3; also elsewhere on the board
/RIN_D: J2.4; also elsewhere on the board
/RIN_E: J2.5; also elsewhere on the board
/RIN_F: J2.6; also elsewhere on the board
/RIN_G: J2.7; also elsewhere on the board
/RIN_H: J2.8; also elsewhere on the board
/RIN_I: J2.9; also elsewhere on the board
/RIN_J: J2.10; also elsewhere on the board
/RIN_K: J2.11; also elsewhere on the board
/RIN_L: J2.12; also elsewhere on the board
/RIN_M: J2.13; also elsewhere on the board
/RIN_N: J2.14; also elsewhere on the board
/RIN_O: J2.15; also elsewhere on the board
/RIN_P: J2.16; also elsewhere on the board
/RIN_Q: J2.17; also elsewhere on the board
/RIN_R: J2.18; also elsewhere on the board
/RIN_S: J2.19; also elsewhere on the board
/RIN_T: J2.20; also elsewhere on the board
/RIN_U: J2.21; also elsewhere on the board
/RIN_V: J2.22; also elsewhere on the board
/RIN_W: J2.23; also elsewhere on the board
/RIN_X: J2.24; also elsewhere on the board
/RIN_Y: J2.25; also elsewhere on the board
/RIN_Z: J2.26; also elsewhere on the board
/ROUT_A: J4.1; also elsewhere on the board
/ROUT_B: J4.2; also elsewhere on the board
/ROUT_C: J4.3; also elsewhere on the board
/ROUT_D: J4.4; also elsewhere on the board
/ROUT_E: J4.5; also elsewhere on the board
/ROUT_F: J4.6; also elsewhere on the board
/ROUT_G: J4.7; also elsewhere on the board
/ROUT_H: J4.8; also elsewhere on the board
/ROUT_I: J4.9; also elsewhere on the board
/ROUT_J: J4.10; also elsewhere on the board
/ROUT_K: J4.11; also elsewhere on the board
/ROUT_L: J4.12; also elsewhere on the board
/ROUT_M: J4.13; also elsewhere on the board
/ROUT_N: J4.14; also elsewhere on the board
/ROUT_O: J4.15; also elsewhere on the board
/ROUT_P: J4.16; also elsewhere on the board
/ROUT_Q: J4.17; also elsewhere on the board
/ROUT_R: J4.18; also elsewhere on the board
/ROUT_S: J4.19; also elsewhere on the board
/ROUT_T: J4.20; also elsewhere on the board
/ROUT_U: J4.21; also elsewhere on the board
/ROUT_V: J4.22; also elsewhere on the board
/ROUT_W: J4.23; also elsewhere on the board
/ROUT_X: J4.24; also elsewhere on the board
/ROUT_Y: J4.25; also elsewhere on the board
/ROUT_Z: J4.26; also elsewhere on the board

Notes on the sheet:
CHASSIS (decision 0003 7.1): D-sub shells J1-J5 (footprint pads SH) and mounting holes H1-H4 = CHASSIS, not 0 V. R6 1 Mohm || C1 10 nF/100 V between CHASSIS and 0 V (electrostatic path, open for DC). J1-J4 pins 27-29 are not connected here (0003 5.2: the 0 V reference is tied on the common side onl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
Relay shifter board - one shifter pair (outbound + return halves share the coils) Connectors: J1 outbound IN, J2 return IN (one board edge); J3 outbound OUT, J4 return OUT (opposite edge); J5 control. D-sub 37: pins 1-26 = lines A-Z (as unit tester J_A/J_B), 27-29 = 0 V reference, NOT connected her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
